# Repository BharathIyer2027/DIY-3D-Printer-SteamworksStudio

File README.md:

# DIY-3D-Printer-SteamworksStudio
Custom ESP32 board based off ESP32 Helios model and Marlin firmware configured for wooden framed creality board printer

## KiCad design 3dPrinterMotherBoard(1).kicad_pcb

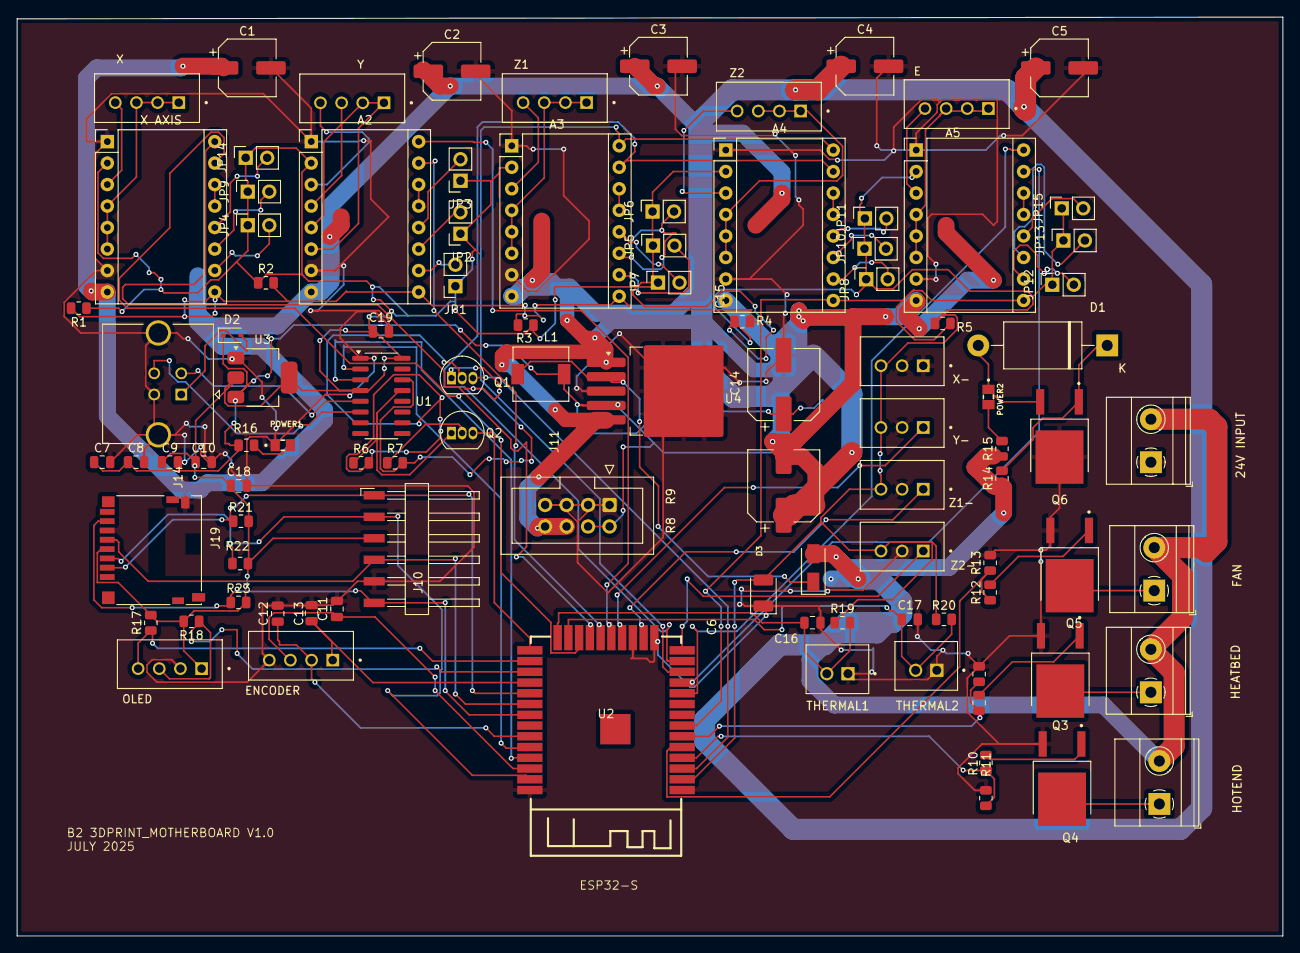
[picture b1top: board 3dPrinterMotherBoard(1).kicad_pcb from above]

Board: 4 copper layers, 149.6 x 108.6 mm, 99 parts (0 on the bottom side), 82 nets.

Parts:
24V INPUT: Screw_Terminal_01x02; TerminalBlock_Phoenix_MKDS-1,5-2-5.08_1x02_P5.08mm_Horizont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
A2: Y; Pololu_Breakout-16_15.2x20.3mm
A3: Z1; Pololu_Breakout-16_15.2x20.3mm
A4: Z2; Pololu_Breakout-16_15.2x20.3mm
A5: E; Pololu_Breakout-16_15.2x20.3mm
C1, C2, C3, C4, C5: 47 uF 35V; CP_Elec_6.3x5.9
C6: 100uF; CP_EIA-3528-15_AVX-H
C7, C9, C18: 0.1uF; C_0805_2012Metric
C8, C10, C16, C17, C19: 10uF; C_0805_2012Metric
C11, C12, C13: 100nf; C_0805_2012Metric
C14: 220uF 50V; CP_Elec_8x6.9
C15: 100uF 50V; CP_Elec_8x6.9
D1: 1.5KE18A; D_DO-201AE_P15.24mm_Horizontal
D2: 1N5819WS; D_SOD-323
D3: SS54; DO-214AC
E: B4B-XH-A_LF__SN_; JST_B4B-XH-A_LF__SN_
ENCODER: B4B-XH-A_LF__SN_; JST_B4B-XH-A_LF__SN_
FAN: Screw_Terminal_01x02; TerminalBlock_Phoenix_MKDS-1,5-2-5.08_1x02_P5.08mm_Horizont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
HEATBED: Screw_Terminal_01x02; TerminalBlock_Phoenix_MKDS-1,5-2-5.08_1x02_P5.08mm_Horizont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
HOTEND: Screw_Terminal_01x02; TerminalBlock_Phoenix_MKDS-1,5-2-5.08_1x02_P5.08mm_Horizont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
J10: Conn_01x06_Pin; Harwin_M20-89006xx_1x06_P2.54mm_Horizontal
J11: Conn_02x04_Odd_Even; IDC-Header_2x04_P2.54mm_Vertical
J14: USB_B; USB_B_TE_5787834_Vertical
J19: Micro_SD_Card; microSD_HC_Hirose_DM3D-SF
JP1, JP2, JP3, JP4, JP5, JP6, JP7, JP8, JP9, JP10, JP11, JP12, JP13, JP14, JP15: Jumper_2_Bridged; PinSocket_1x02_P2.54mm_Vertical
L1: 33uH; L_6.3x6.3_H3
OLED: B4B-XH-A_LF__SN_; JST_B4B-XH-A_LF__SN_
POWER1, POWER2: SML-LXT0805IW-TR; LEDC2012X120N
Q1, Q2: S8050; TO-92_Inline
Q3, Q4, Q5, Q6: AOD4184A; DPAK228P994X240-4N
R1, R2, R3, R4, R5, R21, R22, R23: 10K; R_0805_2012Metric
R6, R7: 12K; R_0805_2012Metric
R8, R10, R12: 10R; R_0805_2012Metric
R9, R11, R13: 100k; R_0805_2012Metric
R14, R15, R16: 1K; R_0805_2012Metric
R17, R18, R19, R20: 4.7K; R_0805_2012Metric
THERMAL1, THERMAL2: B2B-XH-A__LF__SN_; JST_B2B-XH-A__LF__SN_
U1: CH340C; SOIC-16_3.9x9.9mm_P1.27mm
U2: 2.4GHz; ESP32-S
U3: AMS1117-3.3; SOT-223-3_TabPin2
U4: LM2596S-5; TO-263-5_TabPin3
X : B4B-XH-A_LF__SN_; JST_B4B-XH-A_LF__SN_
X AXIS: X; Pololu_Breakout-16_15.2x20.3mm
X-: B3B-XH-A_LF__SN_; JST_B3B-XH-A_LF__SN_
Y : B4B-XH-A_LF__SN_; JST_B4B-XH-A_LF__SN_
Y-: B3B-XH-A_LF__SN_; JST_B3B-XH-A_LF__SN_
Z1, Z2: B4B-XH-A_LF__SN_; JST_B4B-XH-A_LF__SN_
Z1-, Z2-: B3B-XH-A_LF__SN_; JST_B3B-XH-A_LF__SN_

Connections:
+5V: C7.1, C8.1, C14.1, D2.1 (K), J11.2, J11.4, L1.2, R16.1, U3.3 (VI), U4.4 (FB)
+24V: 24V INPUT.2, A2.8 (VMOT), A3.8 (VMOT), A4.8 (VMOT), A5.8 (VMOT), C1.1, C2.1, C3.1, C4.1, C5.1, C15.1, C15.2, D3.A, FAN.2, HEATBED.2, HOTEND.2, J11.6, J11.8, R14.1, R15.1, U4.1 (VIN), U4.5 (~ON/OFF), X AXIS.8 (VMOT)
EN: Q1.3 (C), U2.3 (EN)
GND: 24V INPUT.1, A2.1 (GND), A2.7 (GND), A3.1 (GND), A3.7 (GND), A4.1 (GND), A4.7 (GND), A5.1 (GND), A5.7 (GND), C1.2, C2.2, C3.2, C4.2, C5.2, C6.1, C7.2, C8.2, C9.2, C10.2, C11.2, C12.2, C13.2, C14.2, C16.2, C17.2, C18.2, C19.2, ENCODER.4, J10.5, J11.1, J11.3, J11.5, J11.7, J14.4 (GND), J14.5 (Shield), J19.6 (VSS), J19.9 (SHIELD), OLED.2, POWER1.C, Q3.3, Q4.3, Q5.3, Q6.4, R9.2, R11.2, R13.2, THERMAL1.1, THERMAL2.1, U1.1 (GND), U2.1 (GND), U2.15 (GND), U2.17 (SD2), U2.38 (GND), U3.1 (GND), U4.3 (GND), X AXIS.1 (GND), X AXIS.7 (GND), X-.1, X-.2, Y-.2, Z1-.2, Z2-.2
IO0: Q2.3 (C), U2.25 (IO0)
IO02: C16.1, R19.2, THERMAL1.2, U2.24 (IO2)
IO04: OLED.4, R17.1, U2.26 (IO4)
IO05: J10.1, J19.2 (DAT3/CD), R21.1, U2.29 (IO5)
IO07: U2.21 (SDO), X AXIS.16 (DIR)
IO08: U2.22 (SDI), X AXIS.15 (STEP)
IO09: U2.18 (SD3), Y-.1
IO11: A2.16 (DIR), U2.19 (CMD)
IO12: U2.14 (IO12), Z2-.1
IO13: U2.16 (IO13), Z1-.1
IO14: A3.15 (STEP), A4.15 (STEP), U2.13 (IO14)
IO15: C17.1, R20.2, THERMAL2.2, U2.23 (IO15)
IO16: OLED.3, R18.1, U2.27 (IO16)
IO17: C13.1, ENCODER.1, U2.28 (IO17)
IO18: J10.4, J19.5 (CLK), U2.30 (IO18)
IO19: J10.6, J19.7 (DAT0), R23.1, U2.31 (IO19)
IO20: A2.15 (STEP), U2.20 (CLK)
IO21: C12.1, ENCODER.2, U2.33 (IO21)
IO22: C11.1, ENCODER.3, U2.36 (IO22)
IO23: J10.2, J19.3 (CMD), R22.1, U2.37 (IO23)
IO25: A5.16 (DIR), U2.10 (IO25)
IO26: A5.15 (STEP), U2.11 (IO26)
IO27: A3.16 (DIR), A4.16 (DIR), U2.12 (IO27)
IO34: R8.1, R9.1, U2.6 (IO34)
IO35: A2.9 (~ENABLE), A3.9 (~ENABLE), A4.9 (~ENABLE), A5.9 (~ENABLE), R1.2, R2.2, R3.2, R4.2, R5.2, U2.7 (IO35), X AXIS.9 (~ENABLE)
IO36: R12.1, R13.1, U2.5 (SENSOR_VN)
IO39: R10.1, R11.1, U2.4 (SENSOR_VP)
unnamed: X.1, X.2, X.3, X AXIS.4 (1A), X AXIS.5 (2A), X AXIS.6 (2B)
unnamed: X.4, X AXIS.3 (1B)
unnamed: JP4.2 (B), X AXIS.10 (MS1)
unnamed: JP9.2 (B), X AXIS.11 (MS2)
unnamed: JP14.2 (B), X AXIS.12 (MS3)
unnamed: X AXIS.13 (~RESET), X AXIS.14 (~SLEEP)
unnamed: A2.4 (1A), A2.5 (2A), A2.6 (2B), Y.1, Y.2, Y.3
unnamed: A2.3 (1B), Y.4
unnamed: A2.10 (MS1), JP1.2 (B)
unnamed: A2.11 (MS2), JP2.2 (B)
unnamed: A2.12 (MS3), JP3.2 (B)
unnamed: A2.13 (~RESET), A2.14 (~SLEEP)
unnamed: A3.4 (1A), A3.5 (2A), A3.6 (2B), Z1.1, Z1.2, Z1.3
unnamed: A3.3 (1B), Z1.4
unnamed: A3.10 (MS1), JP5.2 (B)
unnamed: A3.11 (MS2), JP6.2 (B)
unnamed: A3.12 (MS3), JP7.2 (B)
unnamed: A3.13 (~RESET), A3.14 (~SLEEP)
unnamed: A4.4 (1A), A4.5 (2A), A4.6 (2B), Z2.1, Z2.2, Z2.3
unnamed: A4.3 (1B), Z2.4
unnamed: A4.10 (MS1), JP8.2 (B)
unnamed: A4.11 (MS2), JP10.2 (B)
unnamed: A4.12 (MS3), JP11.2 (B)
unnamed: A4.13 (~RESET), A4.14 (~SLEEP)
unnamed: A5.4 (1A), A5.5 (2A), A5.6 (2B), E.1, E.2, E.3
unnamed: A5.3 (1B), E.4
unnamed: A5.10 (MS1), JP12.2 (B)
unnamed: A5.11 (MS2), JP13.2 (B)
unnamed: A5.12 (MS3), JP15.2 (B)
unnamed: A5.13 (~RESET), A5.14 (~SLEEP)
unnamed: D1.1 (A1), Q6.1, R14.2
unnamed: D1.2 (A2), POWER2.C, Q6.3
unnamed: D2.2 (A), J14.1 (VBUS)
unnamed: FAN.1, Q5.4
unnamed: HOTEND.1, Q4.4
unnamed: HEATBED.1, Q3.4
unnamed: POWER1.A, R16.2
unnamed: POWER2.A, R15.2
unnamed: Q1.2 (B), R6.2
unnamed: Q1.1 (E), R7.2, U1.14 (~RTS)
unnamed: Q2.2 (B), R7.1
unnamed: Q2.1 (E), R6.1, U1.13 (~DTR)
unnamed: Q3.1, R8.2
unnamed: Q4.1, R10.2
unnamed: Q5.1, R12.2
unnamed: D3.C, L1.1, U4.2 (OUT)
U0RX: U1.2 (TXD), U2.34 (U0RXD)
U0TX: U1.3 (RXD), U2.35 (U0TXD)
UD+: J14.2 (D-), U1.5 (UD+)
UD-: J14.3 (D+), U1.6 (UD-)
VDD3V3: A2.2 (VDD), A3.2 (VDD), A4.2 (VDD), A5.2 (VDD), C6.2, C9.1, C10.1, C18.1, C19.1, J10.3, J19.4 (VDD), JP1.1 (A), JP2.1 (A), JP3.1 (A), JP4.1 (A), JP5.1 (A), JP6.1 (A), JP7.1 (A), JP8.1 (A), JP9.1 (A), JP10.1 (A), JP11.1 (A), JP12.1 (A), JP13.1 (A), JP14.1 (A), JP15.1 (A), OLED.1, R1.1, R2.1, R3.1, R4.1, R5.1, R17.2, R18.2, R19.1, R20.1, R21.2, R22.2, R23.2, U1.4 (V3), U1.16 (VCC), U2.2 (3V3), U3.2 (VO), X AXIS.2 (VDD), X-.3, Y-.3, Z1-.3, Z2-.3

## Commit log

2025-08-04 software files
